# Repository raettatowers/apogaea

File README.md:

LED projects
============

Various LED art projects that I use for Apogaea or other festivals.

Bicycle
-------

LED animations for my bicycle. LED strips, spokes, and hopefully more to come.

Goggles
-------

Infinity mirror goggles, inspired/stolen from [theindian08 on
Reddit](https://www.reddit.com/r/arduino/comments/8i6m5w/) Previously this was
Adafruit's [goggle project](https://www.adafruit.com/product/2221). I added a
microphone, some other animations, and a button.

Helmet
------

Some simple animations for a helmeted costume.

Monk
----

I saw [LightStuff infinity mirror
mask](https://www.instagram.com/p/BCwOx3URL7J/) and wanted to make my own.
Animations, button, sound reactive.

Vest
----

Fur vest with LEDs that make it glow. Inspired/stolen from the [LED
vest](https://www.youtube.com/watch?v=J8TyGCo32pY) by
[Finominal](https://github.com/finominal). Check out [their
code](https://github.com/finominal/LedVestPlasmaGenerator).

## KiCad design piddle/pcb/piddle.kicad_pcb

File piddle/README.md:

Piddle
======

Knockoff version of Sound Puddle. Smaller, fewer strips, running on a protoboard ESP32.

Wiring
------

- LED pins: see source
- Microphone
  - SCK: 19
  - WS: 22
  - SD: 21
  - L/R: ground
  - VDD: 3.3V
  - GND: ground

Hardware
--------

- ESP32 WROOM 32
- I2S microphone
- 10 WS2812B LED strips

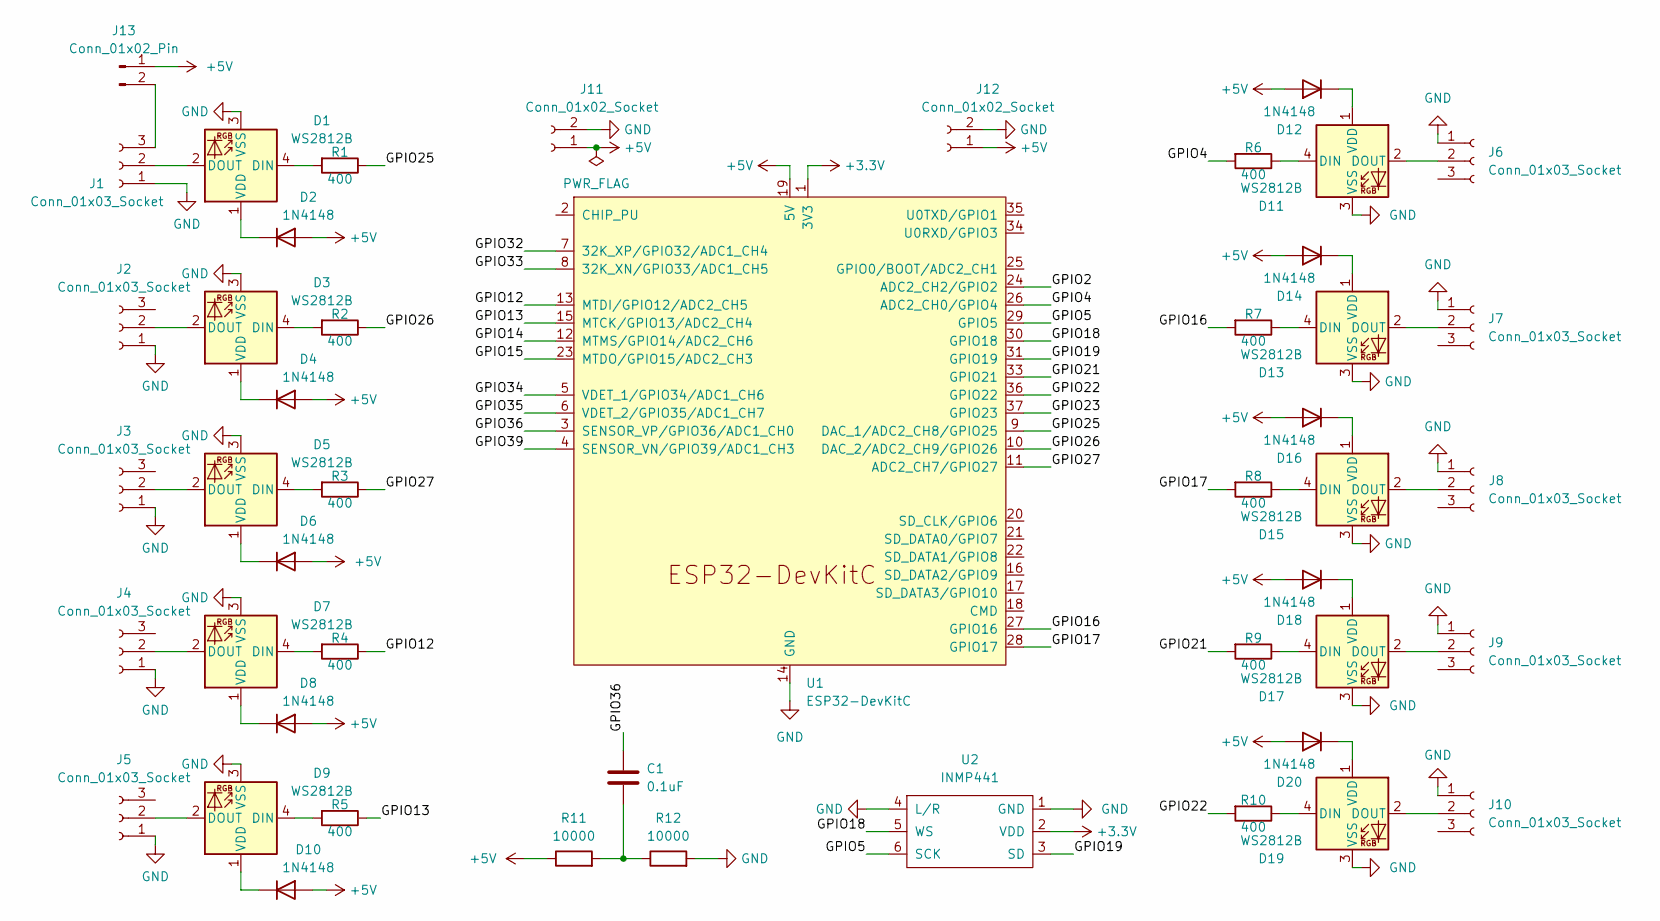
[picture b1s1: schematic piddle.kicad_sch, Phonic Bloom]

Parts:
C1: 0.1uF; C_Disc_D10.0mm_W2.5mm_P5.00mm
D1, D3, D5, D7, D9, D11, D13, D15, D17, D19: WS2812B; LED_WS2812B_PLCC4_5.0x5.0mm_P3.2mm
D2, D4, D6, D8, D10, D12, D14, D16, D18, D20: 1N4148; D_DO-35_SOD27_P10.16mm_Horizontal
J1, J2, J3, J4, J5, J6, J7, J8, J9, J10: Conn_01x03_Socket; PinHeader_1x03_P2.54mm_Vertical
J11, J12: Conn_01x02_Socket; JST_PH_S2B-PH-K_1x02_P2.00mm_Horizontal
J13: Conn_01x02_Pin; PinHeader_1x02_P2.54mm_Vertical
R1, R2, R3, R4, R5, R6, R7, R8, R9, R10: 400; R_Axial_DIN0207_L6.3mm_D2.5mm_P10.16mm_Horizontal
R11, R12: 10000; R_Axial_DIN0207_L6.3mm_D2.5mm_P10.16mm_Horizontal
U1: ESP32-DevKitC
U2: INMP441; inmp441

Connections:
+3.3V: U1.1 (3V3), U2.2 (VDD)
+5V: D2.2 (A), D4.2 (A), D6.2 (A), D8.2 (A), D10.2 (A), D12.2 (A), D14.2 (A), D16.2 (A), D18.2 (A), D20.2 (A), J11.1, J12.1, J13.1, R11.1, U1.19 (5V)
/GPIO2: U1.24 (ADC2_CH2/GPIO2)
/GPIO4: R6.2, U1.26 (ADC2_CH0/GPIO4)
/GPIO5: U1.29 (GPIO5), U2.6 (SCK)
/GPIO12: R4.1, U1.13 (MTDI/GPIO12/ADC2_CH5)
/GPIO13: R5.1, U1.15 (MTCK/GPIO13/ADC2_CH4)
/GPIO14: U1.12 (MTMS/GPIO14/ADC2_CH6)
/GPIO15: U1.23 (MTDO/GPIO15/ADC2_CH3)
/GPIO16: R7.2, U1.27 (GPIO16)
/GPIO17: R8.2, U1.28 (GPIO17)
/GPIO18: U1.30 (GPIO18), U2.5 (WS)
/GPIO19: U1.31 (GPIO19), U2.3 (SD)
/GPIO21: R9.2, U1.33 (GPIO21)
/GPIO22: R10.2, U1.36 (GPIO22)
/GPIO23: U1.37 (GPIO23)
/GPIO25: R1.1, U1.9 (DAC_1/ADC2_CH8/GPIO25)
/GPIO26: R2.1, U1.10 (DAC_2/ADC2_CH9/GPIO26)
/GPIO27: R3.1, U1.11 (ADC2_CH7/GPIO27)
/GPIO32: U1.7 (32K_XP/GPIO32/ADC1_CH4)
/GPIO33: U1.8 (32K_XN/GPIO33/ADC1_CH5)
/GPIO34: U1.5 (VDET_1/GPIO34/ADC1_CH6)
/GPIO35: U1.6 (VDET_2/GPIO35/ADC1_CH7)
/GPIO36: C1.1, U1.3 (SENSOR_VP/GPIO36/ADC1_CH0)
/GPIO39: U1.4 (SENSOR_VN/GPIO39/ADC1_CH3)
GND: D1.3 (VSS), D3.3 (VSS), D5.3 (VSS), D7.3 (VSS), D9.3 (VSS), D11.3 (VSS), D13.3 (VSS), D15.3 (VSS), D17.3 (VSS), D19.3 (VSS), J1.1, J2.1, J3.1, J4.1, J5.1, J6.1, J7.1, J8.1, J9.1, J10.1, J11.2, J12.2, R12.2, U1.14 (GND), U1.32 (GND), U1.38 (GND), U2.1 (GND), U2.4 (L/R); also elsewhere on the board
unnamed: C1.2, R11.2, R12.1
unnamed: D1.4 (DIN), R1.2
unnamed: D1.2 (DOUT), J1.2
unnamed: D1.1 (VDD), D2.1 (K)
unnamed: D3.4 (DIN), R2.2
unnamed: D3.2 (DOUT), J2.2
unnamed: D3.1 (VDD), D4.1 (K)
unnamed: D5.4 (DIN), R3.2
unnamed: D5.2 (DOUT), J3.2
unnamed: D5.1 (VDD), D6.1 (K)
unnamed: D7.4 (DIN), R4.2
unnamed: D7.2 (DOUT), J4.2
unnamed: D7.1 (VDD), D8.1 (K)
unnamed: D9.4 (DIN), R5.2
unnamed: D9.2 (DOUT), J5.2
unnamed: D9.1 (VDD), D10.1 (K)
unnamed: D11.4 (DIN), R6.1
unnamed 43: D11.2 (DOUT), J6.2; also elsewhere on the board
unnamed: D11.1 (VDD), D12.1 (K)
unnamed: D13.4 (DIN), R7.1
unnamed: D13.2 (DOUT), J7.2
unnamed: D13.1 (VDD), D14.1 (K)
unnamed: D15.4 (DIN), R8.1
unnamed: D15.2 (DOUT), J8.2
unnamed: D15.1 (VDD), D16.1 (K)
unnamed: D17.4 (DIN), R9.1
unnamed: D17.2 (DOUT), J9.2
unnamed: D17.1 (VDD), D18.1 (K)
unnamed: D19.4 (DIN), R10.1
unnamed: D19.2 (DOUT), J10.2
unnamed: D19.1 (VDD), D20.1 (K)
unnamed: J1.3, J13.2

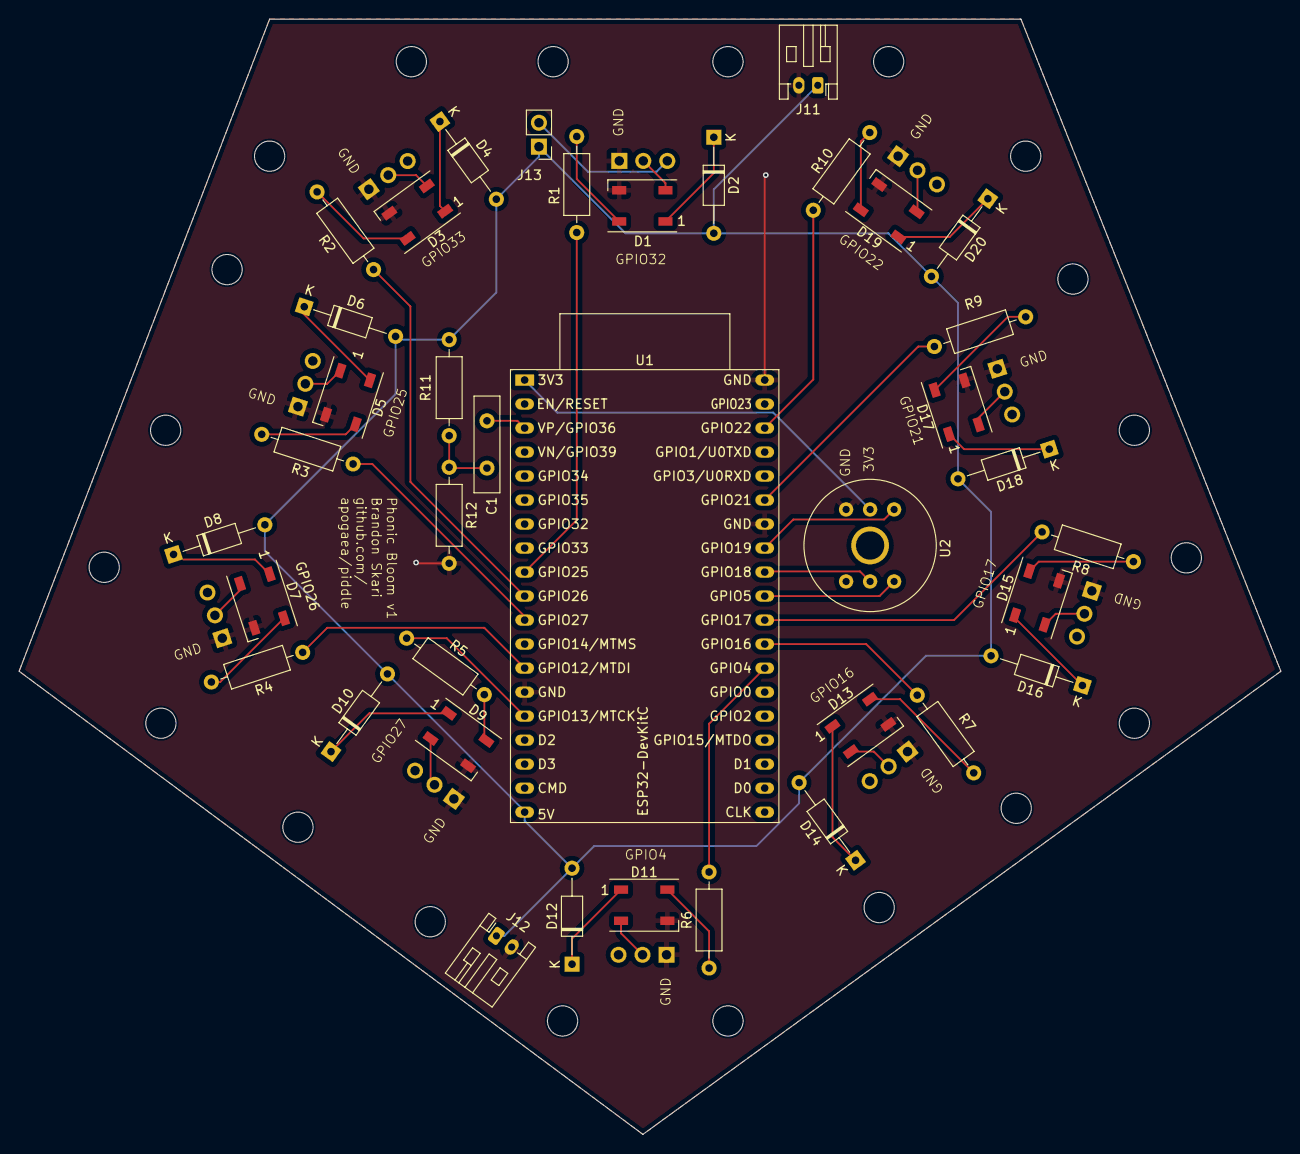
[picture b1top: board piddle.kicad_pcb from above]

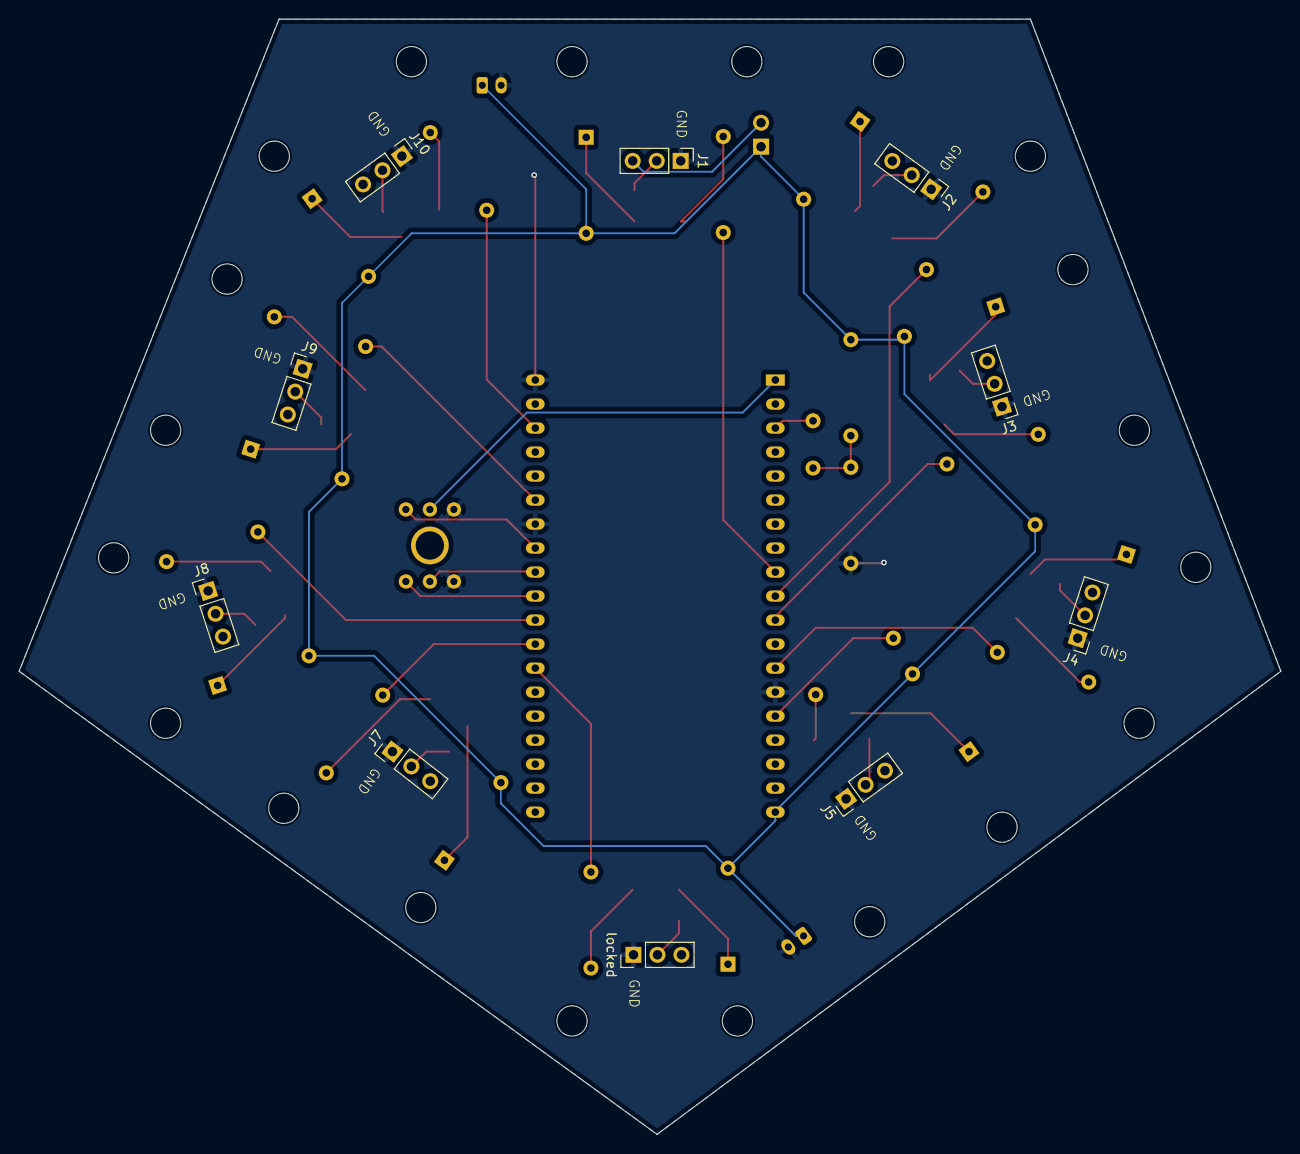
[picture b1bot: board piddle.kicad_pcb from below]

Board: 2 copper layers, 133.5 x 118.0 mm, 48 parts (10 on the bottom side), 49 nets.

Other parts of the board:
locked: Conn_01x03_Socket; PinHeader_1x03_P2.54mm_Vertical

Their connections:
GND: locked.1; also elsewhere on the board
unnamed 43: locked.2; also elsewhere on the board

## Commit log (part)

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2018-06-03 Move modes into separate functions
2018-06-03 Comment out code to prevent compiler errors
2018-06-04 Add binary clock and disable spectrum analyzer
    I couldn't get the microphone to work, so disable it for now. I was also
    just over the ROM size limit with my 3 animations. I added some more
    colors too.
2018-06-04 Start helmet
2018-06-05 Change how wait for button press works
2018-06-05 Change color by holding down the button
2018-06-07 Add mode switching; add party and Knight Rider modes
2019-06-21 Use bitshift instead of integer division
2019-07-03 Fix taking readings from the microphone
    I had to set analogReference to DEFAULT
2019-07-05 SPectrum analyzer working!
2019-07-05 Change colors to a rainbow
2019-07-05 Use function pointers and fix color changing
2019-07-07 Add swirls, fadingSparks, and shimmer animations
2019-07-13 Make the internal pixel transition colors
2019-07-15 Spectrum analyzer working
2019-08-03 Disable internal pixel
2019-08-03 Spectrum analyzer code cleanup
2019-08-03 Button moves between animation lists
2019-08-04 Start separating out the animations
2019-08-04 Separate out animation files
2019-08-08 Fix ripples
2019-08-09 Add flash to beat
2019-08-09 Add rotate gears to beat
2019-08-10 Long press button for brightness configuration
2019-08-11 Use a state machine to handle button presses
    This still has a problem where animations that are calling delay will
    ignore button presses if they happen during the delay. This should use
    an interrupt.
2019-08-11 Add button to interrupt to never miss presses
2019-08-12 Get adaptive beat detection algorithm working; it sucks
    I tested it with my Bluetooth speaker, but it rarely detected stuff.
    Maybe I should just go simpler.
2019-08-31 Change FFT to use floats instead of doubles
    I get about 4X the performance! 66 updates per second versus ~13 with
    the double version.
2019-09-04 Add Newton's cradle animation
2019-09-04 Add rainbow swirls
2019-09-04 Add look around animation
2019-09-11 Fix off by one error
2019-09-16 Add circular wipe and Pac-Man animations (untested)
2019-09-19 Clean up some warnings
2019-10-03 Initial commit of monk mask
2019-10-05 Convert goggle to using FastLED (untested)
2019-10-13 Add test sketch for single LED
2019-10-19 Add some testing for solder/connections functions
2019-10-20 Add button configuration and split out animations
2019-10-20 Add PacMan animation
2019-10-20 Fix some errors from the converstion to FastLED
2019-10-30 Push button to change animations
2019-10-30 Add spectrum analyzer
2019-10-31 Make breathe less bright
2019-10-31 Make circular wipe's leading edge bright then fade
2019-10-31 Make rainbow swirl have 2 and change faster
2020-02-16 Change button behavior to be more consistent
    Originally I had a 2-wire setup for the button, whereas most tutorials
    recommend doing a 3-wire setup with a resistor. But it wasn't reliable,
    probably because I had a short so that pressing the button didn't do
    anything because I'm a dingo.
2020-02-18 Reduce the intensity of lower pitch sounds
    They were drowning out the visualization
2021-06-07 Add goggles and helmet
2021-06-21 Add vest
2021-06-28 Add bicycle animations
2021-06-28 Add button to switch colors
2021-07-03 Add button to vest test program
2021-07-10 Add skeleton for demoing vest
2021-08-03 Start adding demo stuff
2021-08-11 Remove LedArray.hpp
2021-08-12 Add demo
2021-08-13 Fix reversing of LEDs on even strips
2021-08-18 Add shimmer effect
2021-08-28 Add button and blob animation
2021-08-28 Typecast COUNT_OF to int to ignore unsigned comparison warnings
2021-08-28 Have button cycle between sets of animations
2021-08-29 Switch to using signed ints for offsets
2021-08-29 Add blob animation
2021-08-29 Support multiple snakes
2021-09-06 Change how demo works and add some test plasma effects
2021-09-06 Rings animation with sin16 working
2021-09-06 Add pastel colors to demo
2021-09-06 Add fire effect
2021-09-07 Add palette test and fix bug in plasma3
2021-09-08 Add destructor for Snake animation
2021-09-09 Add scons command to rebuild offsets.hpp
2021-09-09 Add Bidoulle animations
2021-09-13 Fix p4
    I'm using floating point to compute some values, but only doing it once
    and then caching them after converting to integers.
2021-09-13 Fix fast Boudille
    I had been missing v3, but now I'm caching it
2021-09-14 Add more blobs and tweak one of the plasmas
    The vest front on one of the plasmas was changing too fast and kind of
    flashing, so tweak it to slow it down
2021-09-14 Move Bidoulle ring offsets calculation to a Python script
2021-09-15 Smooth out the plasma animation to reduce jitter
2021-09-18 Make generated offsets cleaner
2021-09-19 Get videos displaying on the vest
2021-09-21 Add changing color palette
2021-09-25 Add snake game logic
2021-09-26 Run format
2021-09-26 Add READMEs
2021-09-26 Add rainbow spiral calculations
2021-09-27 Add spiral to vest
2021-10-15 Add better FPS to video preprocessor
2021-10-16 Add fullish screen and grayscale spirals
2021-10-20 Add Bluefruit color test
2021-11-09 Change bicycle to use Adafruit's DotStar libraries
    Looks like FastLED has some timing issues with NRF52s and APA102s. See
    the comment BUGBUG in fastspi_arm_nrf52.h
2021-12-02 Make changes to bicycle? I don't know
2022-02-23 Start adding Tetris
2022-02-23 Make Bluefruit test work with external LEDs
2022-02-24 Update goggles for new infinity mirror ones
2022-03-05 Change goggle LEDs to green-blue for infinity mirror
2022-03-06 Add assertion to work around FastLED limitation
    When compiling for nrf52 boards, there is a statically sized array in
    FastLED, but no warning if you try to exceed that limit, which leads to
    some hard to debug problems. Put in a static_assert at least to try to
    detect that error.
2022-03-08 Update READMEs
2022-04-08 Change back to using FastLED
2022-04-08 Start adding ESP32 RemoteXY control
2022-04-30 Add vinyl stencil patterns
2022-05-07 Move bicycle strand animations into separate folder
2022-05-11 Add spokes demo
2022-05-13 Add fading rainbow rings
2022-05-13 Add short and long comet spoke animations
2022-05-13 Remove unused functions from spokes demo
2022-05-13 Make blurred spiral length configurable
2022-05-13 Remove unused arguments
2022-05-14 Each spoke animation returns delay ms
2022-05-15 Add pendulum and orbit spoke animations
2022-05-15 Change spoke count to 9
2022-05-15 Call each animation on startup to initialize
2022-05-15 Add tests
2022-05-15 Add animations and RemoteXY to spokes
2022-05-16 Fix some RemoteXY things
2022-05-16 Add all color and rim color options
2022-05-29 Remove old video stuff from demo
2022-06-04 Add horizontal comets to vest demo
2022-07-03 Add include guard
2022-07-03 Add multiple animations
2022-07-03 Add shade structure cost calculator
2022-07-03 Fix monk mask button
2023-02-19 Add VS Code configuration
2023-04-16 Try to get WiFi OTA updating working
    The sketch is too big though :(
2023-04-16 Add spokes demo README
2023-04-17 Start adding FFT to spokes
    It's not working - I'm getting coredump on core 1
2023-06-08 Update VS Code settings
2023-06-08 First commit of Piddle
2023-06-30 Add compile scripts
2023-06-30 Better dropoff for buckets
2023-06-30 Change buckets
2023-06-30 Better mapping of sample bucket to note bucket
2023-06-30 Remove debug
2023-08-13 Update VS Code
2023-08-13 Spectrum analyzer fixes - slideDown
2023-08-27 STart multicore
2023-08-28 Go back to single-core, drop sample rate and number of buckets
2023-09-10 Add serial dump
2023-09-13 Pretier colors
2023-09-13 Compute C4 index
2023-09-13 Add static assertion
2023-09-15 Add button interrupt
2023-09-23 Find max value in bucket range
2023-09-23 Add RemoteXY configuration
2023-09-23 Update steps
2023-09-23 Fix treble
2023-09-23 Don't normalize the top half of samples
2024-02-15 Vest v2
2024-05-12 Switched black pin to one that works for LEDs
2024-05-12 Update V2 mappings description
2024-05-12 Add config helper RemoteXY program
2024-05-12 Update offset calculation
2024-05-12 Fix some configurations
2024-05-12 Add row and column to helper
2024-05-12 vscode configuration update
2024-05-13 Change animations to use new strand + offset
2024-05-13 Fix LED offsets
2024-05-14 Fix demo
2024-05-15 Define X/Y_CENTER because my LED count is off center
2024-05-20 Use older Python syntax for compatibility
2024-05-28 Reading samples works, had to comment everything out
2024-06-01 Delay when doing multiple DMA reads
2024-06-03 Move microphone pins to other side
2024-06-03 Set correct number of LEDs per strip
2024-06-03 Go back to major steps
2024-06-03 Fix I2S panic
2024-06-03 Conditionally disable RemoteXY
2024-06-03 Do top and bottom of each strip
2024-06-03 Use memmove to move lEDs
2024-09-22 Add Piddle README
2024-09-22 Only have 5 LED strips
2024-09-22 Send data on serial to log debug
2024-10-14 Use RemoteXY_delay
2024-10-14 Fade between animations
2024-10-15 Smoothly fade out/in between animations
2024-10-16 Just use single index offsets for LEDs
    Instead of a 2D array of strand to list of LEDS
2024-10-16 Movie stuff
2024-11-05 Vest movie stuff
2024-11-27 Better performance metrics
2024-12-01 Fix sample collection
2024-12-01 FIx weighting multiplying
2024-12-01 reduce LED count for developing for now
2024-12-02 First attempt, not working
2024-12-03 Actually call spectrum analyzer
2024-12-03 Start task on each core (not working)
2024-12-18 Move constants around
2024-12-18 Restore logging
2024-12-21 Submodules for Piddle microphone component
2024-12-21 FIrst commit of Piddle PCB
2024-12-21 Add resistors for each data line
2024-12-21 Add comments
2024-12-21 Add ground plane on back copper
2024-12-21 Add GPIO silks
2024-12-23 Show time spent calling FastLED.show()
2024-12-23 Fix power nets
2024-12-24 Pigtail strain relief mounting holes
2024-12-24 Add power connectors
2024-12-24 Add jumper for powering board from LED strip
2024-12-24 More connections
2024-12-24 Use SMD resistors
2024-12-24 FLip the connectors
2024-12-25 Gerber stuff
2024-12-25 Switch to plain through holes for LED strip connections
2024-12-28 New I2S API
2024-12-28 e through hole resistors
2024-12-28 Make diodes through hole
2024-12-29 Fix some missed connections. DRC is happy now!
2024-12-30 Copy the most recent samples
2024-12-31 Update ArduinoFFT library
2025-01-01 Fix new I2S API - it's converting signed to unsigned somewhere?
2025-01-01 MOre debug logging
2025-01-01 Fox showing notes on debug logging
2025-01-02 ESP32 FFT test, not working yet
2025-01-02 Fix esp32 fft, and boy is it fast
2025-01-02 Change start note to be higher
    I think my little test Bluetooth speaker can't do low notes very well,
    so for testing, just bump the start note up a bit
2025-01-02 Comment on gamma correction
2025-01-02 Show timings in us instead of ms
    It's too fast now!
2025-01-05 Monitor voltage and show it on the strip
2025-01-05 Keep watchdog happy
2025-01-05 Iterate through rainbow colors
2025-01-05 Add a jump when rolling over strands
2025-01-07 Change data line resistor values
2025-01-07 More labels
2025-01-10 Change the microphone pins to match the PCB
2025-01-20 Change LED pins so they work with WLED
2025-01-26 Use #defines for double ended and show voltage
2025-01-27 Limit current on the USB test strips
2025-01-27 Enforce LEDS_PER_STRIP to be even
2025-01-27 Fix memmove for odd number of LEDs per strip
2025-01-31 Add TODO comment
2025-02-02 Update pins for half-soldered board
2025-02-02 Move delay
2025-02-02 SHow mA too
2025-02-02 Add comment as to why we are delaying
2025-02-02 Press button to change brightness
2025-02-06 Testing stuff for Brandon
2025-02-06 Voltage monitor
2025-02-09 Add relay logic and ADC correction
2025-02-09 Fix linear regression, fix relay toggle delay
2025-02-09 Light sleep
2025-02-17 Add power simulation
2025-02-18 Use my own formula instead of numpy
2025-02-18 Add on-off range
2025-02-18 Add short options
2025-02-21 Remove old info from from README
2025-02-23 Add RemoteXY to voltage monitor
2025-02-24 Add resume % to voltage monitor
2025-03-09 Add infrared receiver
2025-03-16 Add I2SClocklessLedDriver
2025-03-16 Render async
2025-03-16 Revert some stuff back to main
2025-03-20 Basic plotting
